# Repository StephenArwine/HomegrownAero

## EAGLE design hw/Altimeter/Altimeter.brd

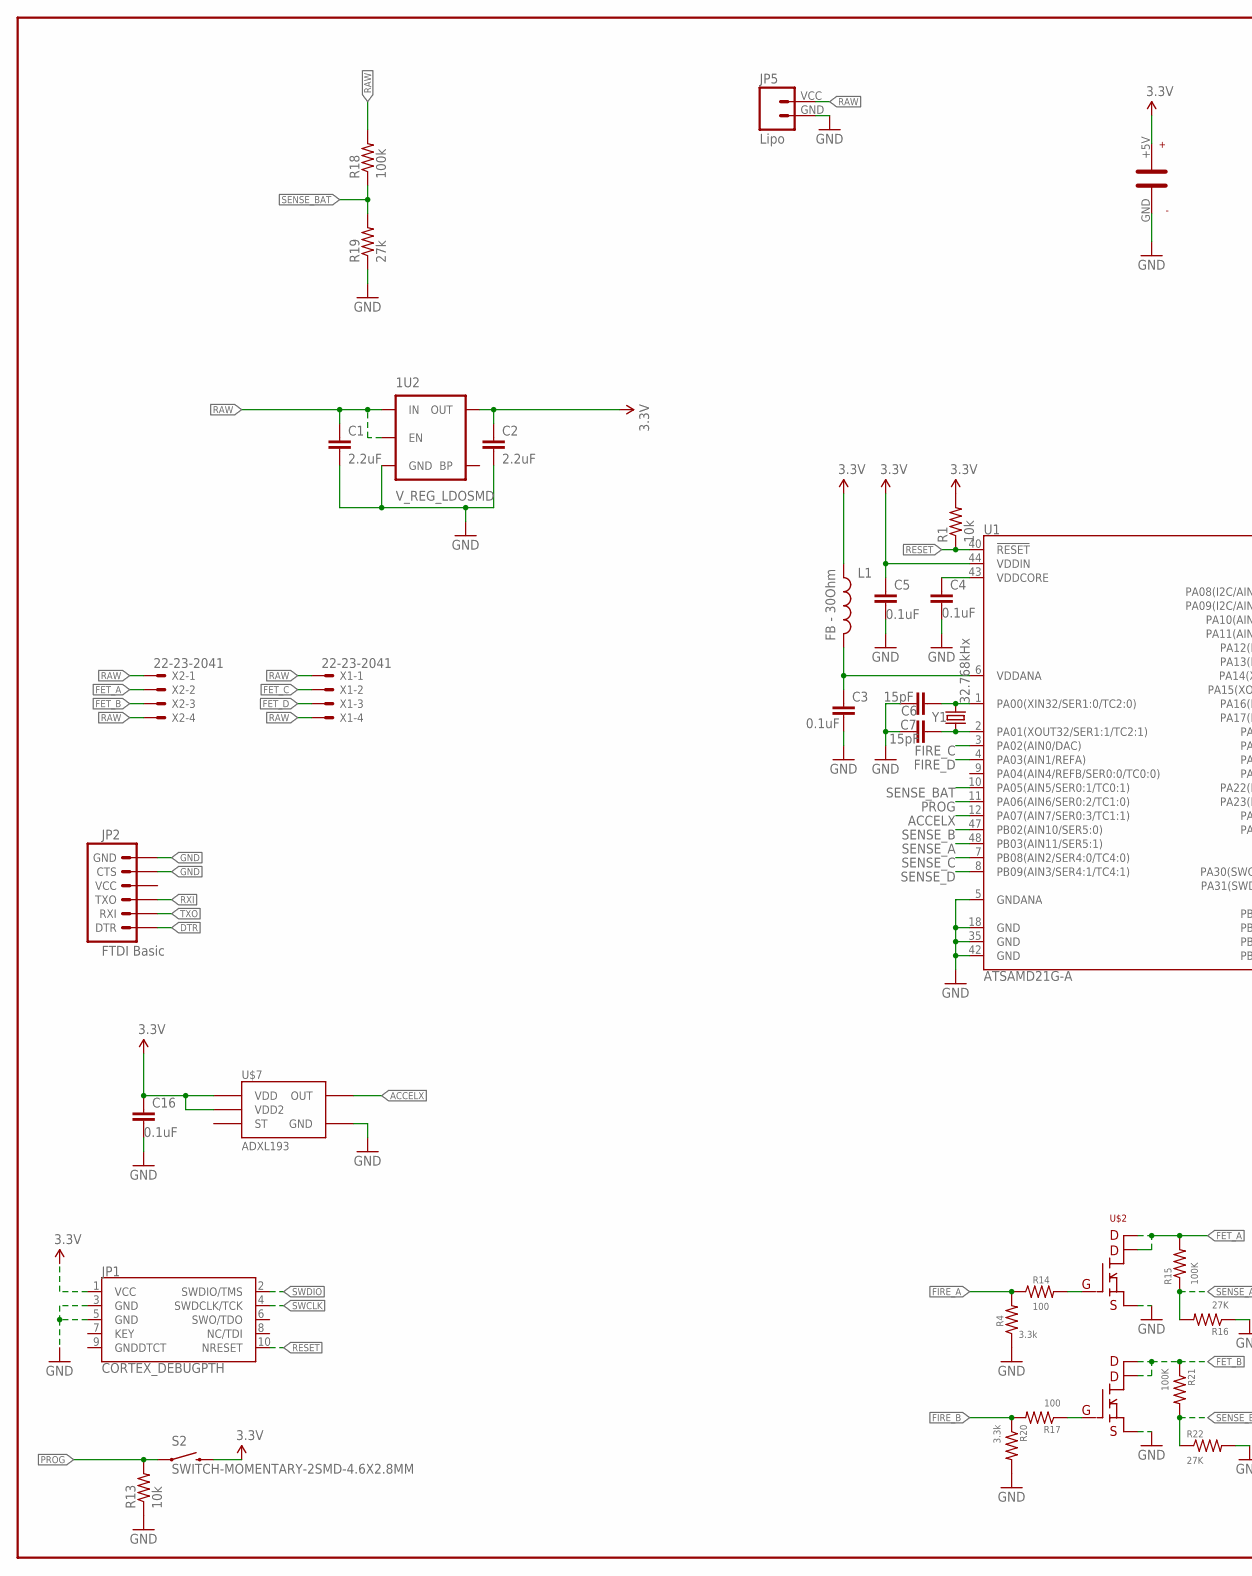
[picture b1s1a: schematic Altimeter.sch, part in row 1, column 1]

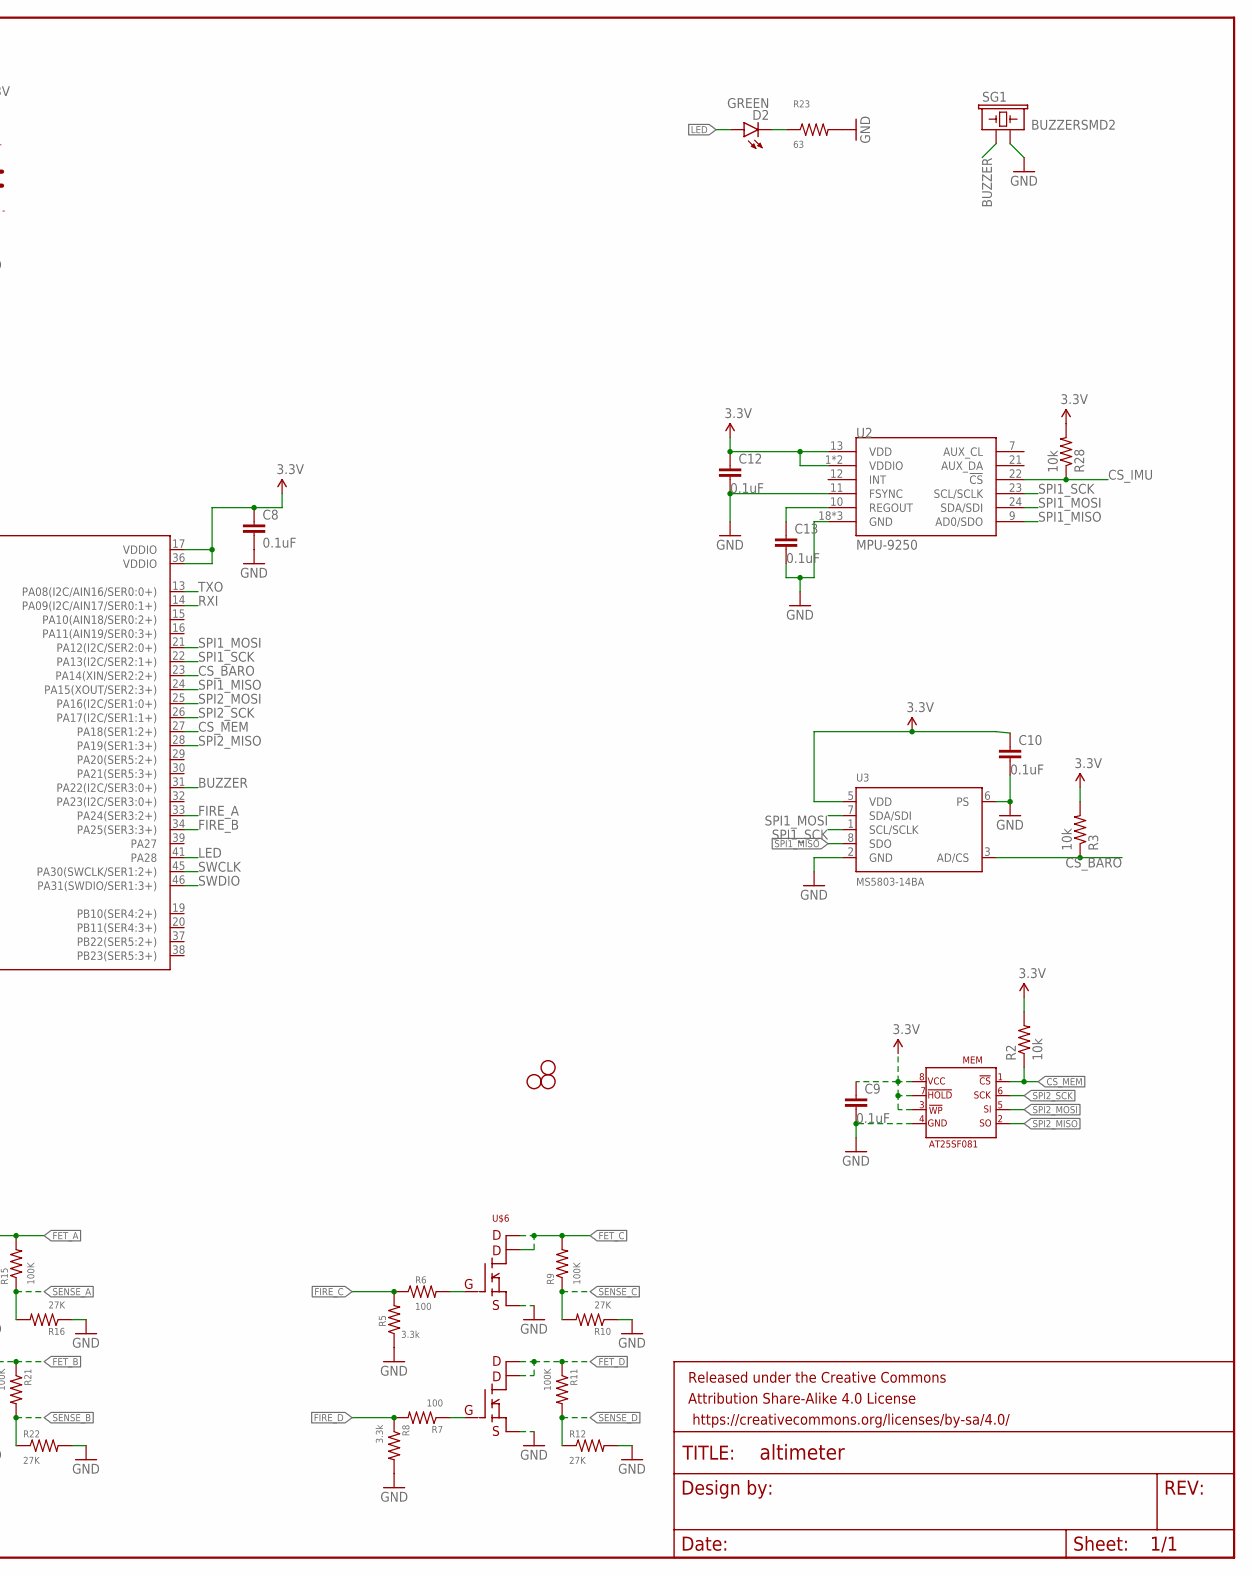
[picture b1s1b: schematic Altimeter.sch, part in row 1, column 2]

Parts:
1U2: V_REG_LDOSMD; SOT23-5
C1, C2: 2.2uF; 0603-CAP
C3, C4, C5, C8, C9, C10, C12, C13, C16: 0.1uF; 0402-CAP
C6, C7: 15pF; 0402-CAP
D2: GREEN; LED-1206
FRAME1: FRAME-LEDGER; CREATIVE_COMMONS
JP1: CORTEX_DEBUGPTH; 2X5-PTH-1.27MM
JP2: FTDI Basic; 1X06
JP5: Lipo; JST-2-SMD-VERT
L1: FB - 30Ohm; 0603
MEM: AT25SF081
R1, R2, R3, R13, R28: 10k; 0402-RES
R4, R5, R8, R20: 3.3k; 0402-RES
R6, R7, R14, R17: 100; 0402-RES
R9, R11, R15, R21: 100K; 0402-RES
R10, R12, R16, R22: 27K; 0402-RES
R18: 100k; 0402-RES
R19: 27k; 0402-RES
R23: 63; 0402-RES
S2: SWITCH-MOMENTARY-2SMD-4.6X2.8MM; TACTILE_SWITCH_SMD_4.6X2.8MM
SG1: BUZZERSMD2; BUZZER-CCV
STANDOFF2, STANDOFF3, STANDOFF4: STAND-OFF
U1: ATSAMD21G-A; TQFP-48
U2: MPU-9250; QFN24_PAD
U3: MS5803-14BA; MS5803
U$1: PB-5R0H104-R
U$2, U$6: SI7232DN
U$7: ADXL193
X1, X2: 22-23-2041
Y1: 32.768kHx; CRYSTAL-SMD-3.2X1.5MM

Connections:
3.3V: 1U2.5 (OUT), C2.1, C5.1, C8.1, C9.1, C10.1, C12.1, C16.1, JP1.1 (VCC), L1.1, MEM.!HOLD, MEM.!WP, MEM.VCC, R1.2, R2.2, R3.2, R28.2, S2.3 (2), S2.4 (2), U1.17 (VDDIO), U1.36 (VDDIO), U1.44 (VDDIN), U2.1 (VDDIO), U2.8 (VDDIO), U2.13 (VDD), U3.5 (VDD), U$1.+5V, U$7.P$7 (VDD), U$7.P$8 (VDD2)
!RESET: JP1.10 (NRESET), R1.1, U1.40 (!RESET!)
ACCELX: U1.12 (PA07(AIN7/SER0:3/TC1:1)), U$7.P$6 (OUT)
BUZZER: SG1.+ (1), U1.31 (PA22(I2C/SER3:0+))
CS_BARO: R3.1, U1.23 (PA14(XIN/SER2:2+)), U3.3 (AD/CS)
CS_IMU: R28.1, U1.29 (PA20(SER5:2+)), U2.22 (!CS)
CS_MEM: MEM.!CS, R2.1, U1.27 (PA18(SER1:2+))
DTR: JP2.1 (DTR)
FET_A: R15.2, U$2.7 (PIN7), U$2.8 (PIN8), X2.2
FET_B: R21.1, U$2.5 (PIN5), U$2.6 (PIN6), X2.3
FET_C: R9.2, U$6.7 (PIN7), U$6.8 (PIN8), X1.2
FET_D: R11.1, U$6.5 (PIN5), U$6.6 (PIN6), X1.3
FIRE_A: R4.2, R14.1, U1.33 (PA24(SER3:2+))
FIRE_B: R17.2, R20.1, U1.34 (PA25(SER3:3+))
FIRE_C: R5.2, R6.1, U1.3 (PA02(AIN0/DAC))
FIRE_D: R7.2, R8.1, U1.4 (PA03(AIN1/REFA))
GND: 1U2.2 (GND), C1.2, C2.2, C3.2, C4.2, C5.2, C6.2, C7.2, C8.2, C9.2, C10.2, C12.2, C13.2, C16.2, JP1.3 (GND), JP1.5 (GND), JP2.5 (CTS), JP2.6 (GND), JP5.GND (1), MEM.GND, R4.1, R5.1, R8.2, R10.1, R12.2, R13.1, R16.1, R19.1, R20.2, R22.2, R23.2, SG1.- (2), U1.5 (GNDANA), U1.18 (GND), U1.35 (GND), U1.42 (GND), U2.11 (FSYNC), U2.18 (GND), U2.20 (GND), U2.CENTER (GND), U3.2 (GND), U3.6 (PS), U$1.GND, U$2.1 (PIN1), U$2.3 (PIN3), U$6.1 (PIN1), U$6.3 (PIN3), U$7.P$3 (GND)
LED: D2.A, U1.41 (PA28)
unnamed: R6.2, U$6.2 (PIN2)
unnamed: C6.1, U1.1 (PA00(XIN32/SER1:0/TC2:0)), Y1.P$2 (2)
unnamed: C7.1, U1.2 (PA01(XOUT32/SER1:1/TC2:1)), Y1.P$1 (1)
unnamed: C3.1, L1.2, U1.6 (VDDANA)
unnamed: C4.1, U1.43 (VDDCORE)
unnamed: R7.1, U$6.4 (PIN4)
unnamed: R14.2, U$2.2 (PIN2)
unnamed: R17.1, U$2.4 (PIN4)
unnamed: D2.C, R23.1
PROG: R13.2, S2.1, S2.2 (1), U1.11 (PA06(AIN6/SER0:2/TC1:0))
RAW: 1U2.1 (IN), 1U2.3 (EN), C1.1, JP5.VCC (2), R18.2, X1.1, X1.4, X2.1, X2.4
REGOUT: C13.1, U2.10 (REGOUT)
RXI: JP2.3 (TXO), U1.14 (PA09(I2C/AIN17/SER0:1+))
SENSE_A: R15.1, R16.2, U1.48 (PB03(AIN11/SER5:1))
SENSE_B: R21.2, R22.1, U1.47 (PB02(AIN10/SER5:0))
SENSE_BAT: R18.1, R19.2, U1.10 (PA05(AIN5/SER0:1/TC0:1))
SENSE_C: R9.1, R10.2, U1.7 (PB08(AIN2/SER4:0/TC4:0))
SENSE_D: R11.2, R12.1, U1.8 (PB09(AIN3/SER4:1/TC4:1))
SPI1_MISO: U1.24 (PA15(XOUT/SER2:3+)), U2.9 (AD0/SDO), U3.8 (SDO)
SPI1_MOSI: U1.21 (PA12(I2C/SER2:0+)), U2.24 (SDA/SDI), U3.7 (SDA/SDI)
SPI1_SCK: U1.22 (PA13(I2C/SER2:1+)), U2.23 (SCL/SCLK), U3.1 (SCL/SCLK)
SPI2_MISO: MEM.SO, U1.28 (PA19(SER1:3+))
SPI2_MOSI: MEM.SI, U1.25 (PA16(I2C/SER1:0+))
SPI2_SCK: MEM.SCK, U1.26 (PA17(I2C/SER1:1+))
SWCLK: JP1.4 (SWDCLK/TCK), U1.45 (PA30(SWCLK/SER1:2+))
SWDIO: JP1.2 (SWDIO/TMS), U1.46 (PA31(SWDIO/SER1:3+))
TXO: JP2.2 (RXI), U1.13 (PA08(I2C/AIN16/SER0:0+))

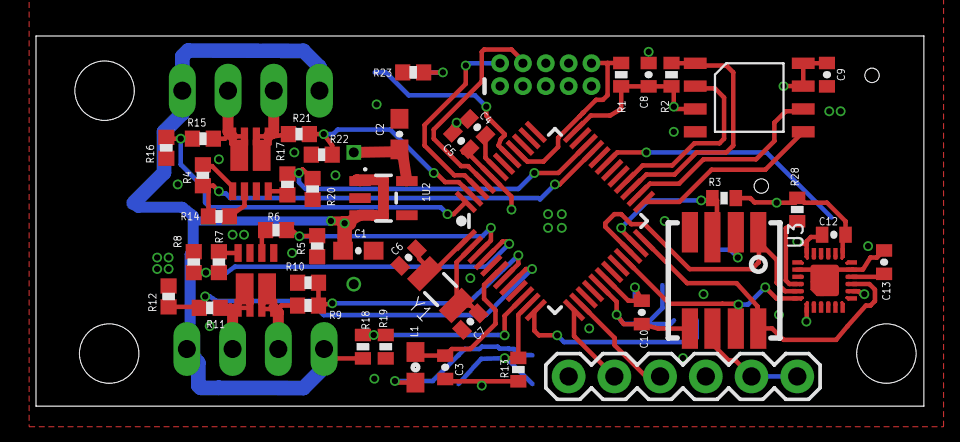
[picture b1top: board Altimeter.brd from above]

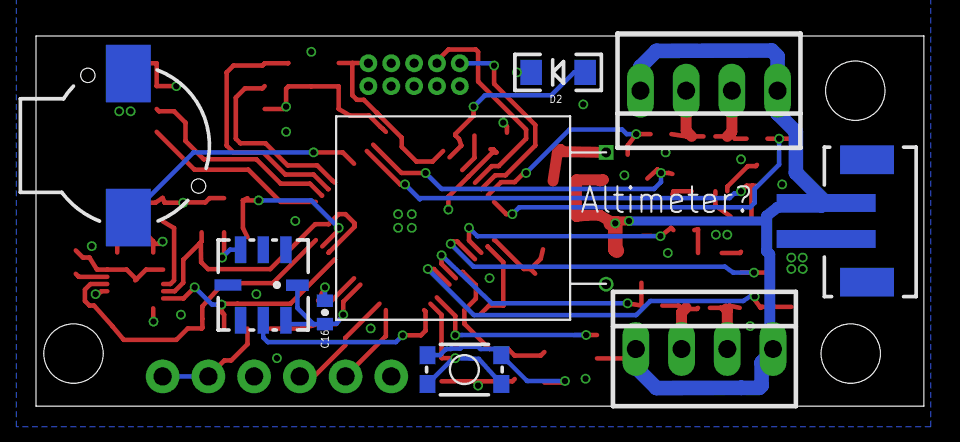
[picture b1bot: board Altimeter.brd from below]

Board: 4 copper layers, 49.3 x 20.6 mm, 60 parts (9 on the bottom side), 44 nets.

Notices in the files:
parts and their libraries:
SparkFun-PowerIC: Licensing: Creative Commons ShareAlike 4.0 International - https://creativecommons.org/licenses/by-sa/4.0
SparkFun-Aesthetics: Released under the Creative Commons Attribution Share-Alike 4.0 License
SparkFun-Aesthetics: https://creativecommons.org/licenses/by-sa/4.0
